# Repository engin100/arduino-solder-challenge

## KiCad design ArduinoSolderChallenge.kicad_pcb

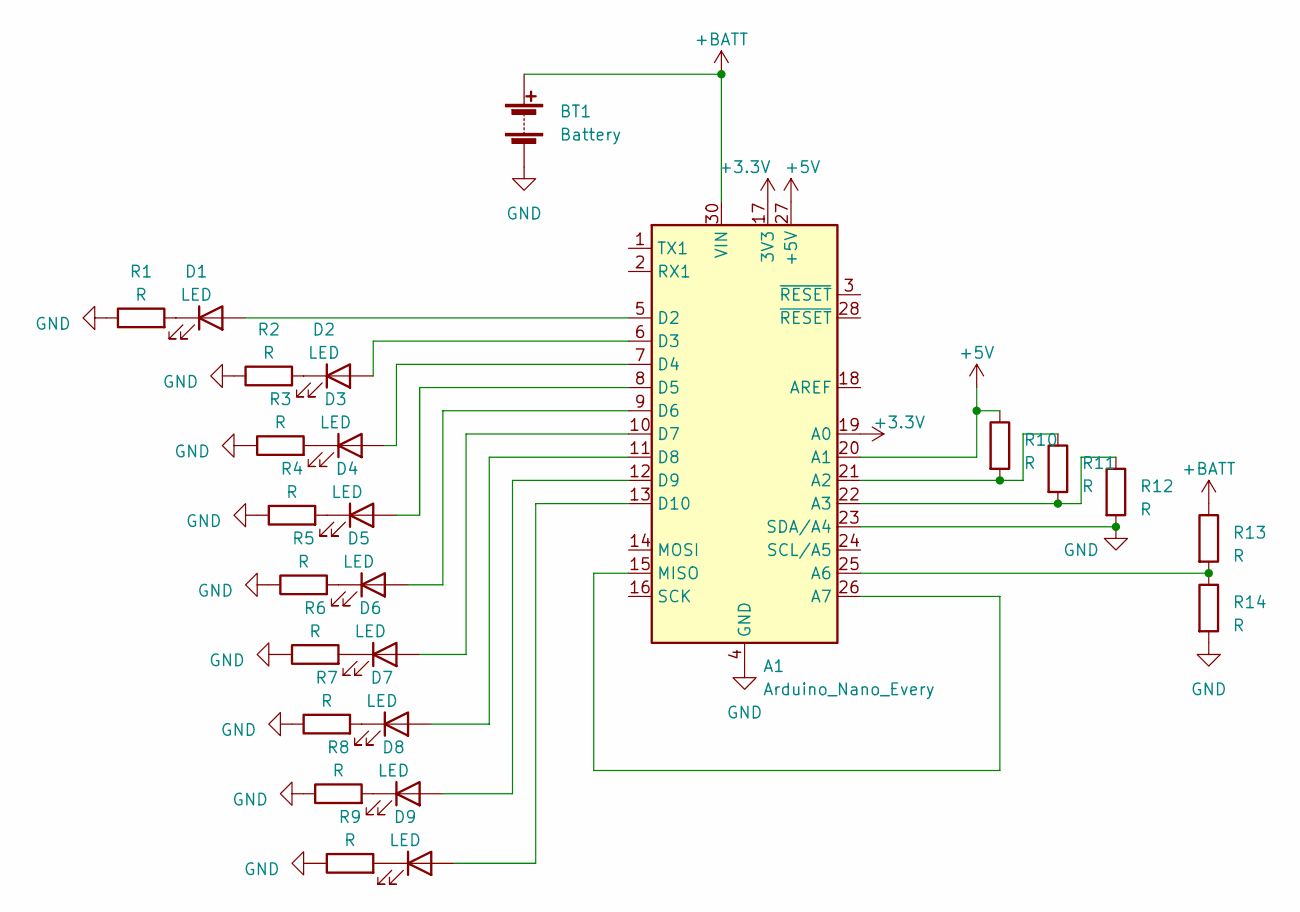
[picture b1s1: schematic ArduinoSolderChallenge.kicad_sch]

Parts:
A1: Arduino_Nano_Every; Arduino_Nano
BT1: Battery; Keystone 967 9V battery holder
D1, D2, D3, D4, D5: LED
D6, D7, D8, D9: LED; LED_1206_3216Metric_Pad1.42x1.75mm_HandSolder
R1, R2, R3, R4, R5, R10, R11, R12: R; Resistor
R6, R7, R8, R9, R13, R14: R; R_1206_3216Metric_Pad1.30x1.75mm_HandSolder

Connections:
+3.3V: A1.17 (3V3), A1.19 (A0)
+5V: A1.20 (A1), A1.27 (+5V), R10.1
+BATT: A1.30 (VIN), BT1.1 (+), R13.1
GND: A1.4 (GND), A1.23 (SDA/A4), A1.29 (GND), BT1.2 (-), R1.1, R2.1, R3.1, R4.1, R5.1, R6.1, R7.1, R8.1, R9.1, R12.2, R14.2
unnamed: A1.21 (A2), R10.2, R11.1
unnamed: A1.22 (A3), R11.2, R12.1
unnamed: A1.25 (A6), R13.2, R14.1
unnamed: A1.15 (MISO), A1.26 (A7)
unnamed: A1.5 (D2), D1.2 (A)
unnamed: A1.6 (D3), D2.2 (A)
unnamed: A1.7 (D4), D3.2 (A)
unnamed: A1.8 (D5), D4.2 (A)
unnamed: A1.9 (D6), D5.2 (A)
unnamed: A1.10 (D7), D6.2 (A)
unnamed: A1.11 (D8), D7.2 (A)
unnamed: A1.12 (D9), D8.2 (A)
unnamed: A1.13 (D10), D9.2 (A)
unnamed: D1.1 (K), R1.2
unnamed: D2.1 (K), R2.2
unnamed: D3.1 (K), R3.2
unnamed: D4.1 (K), R4.2
unnamed: D5.1 (K), R5.2
unnamed: D6.1 (K), R6.2
unnamed: D7.1 (K), R7.2
unnamed: D8.1 (K), R8.2
unnamed: D9.1 (K), R9.2

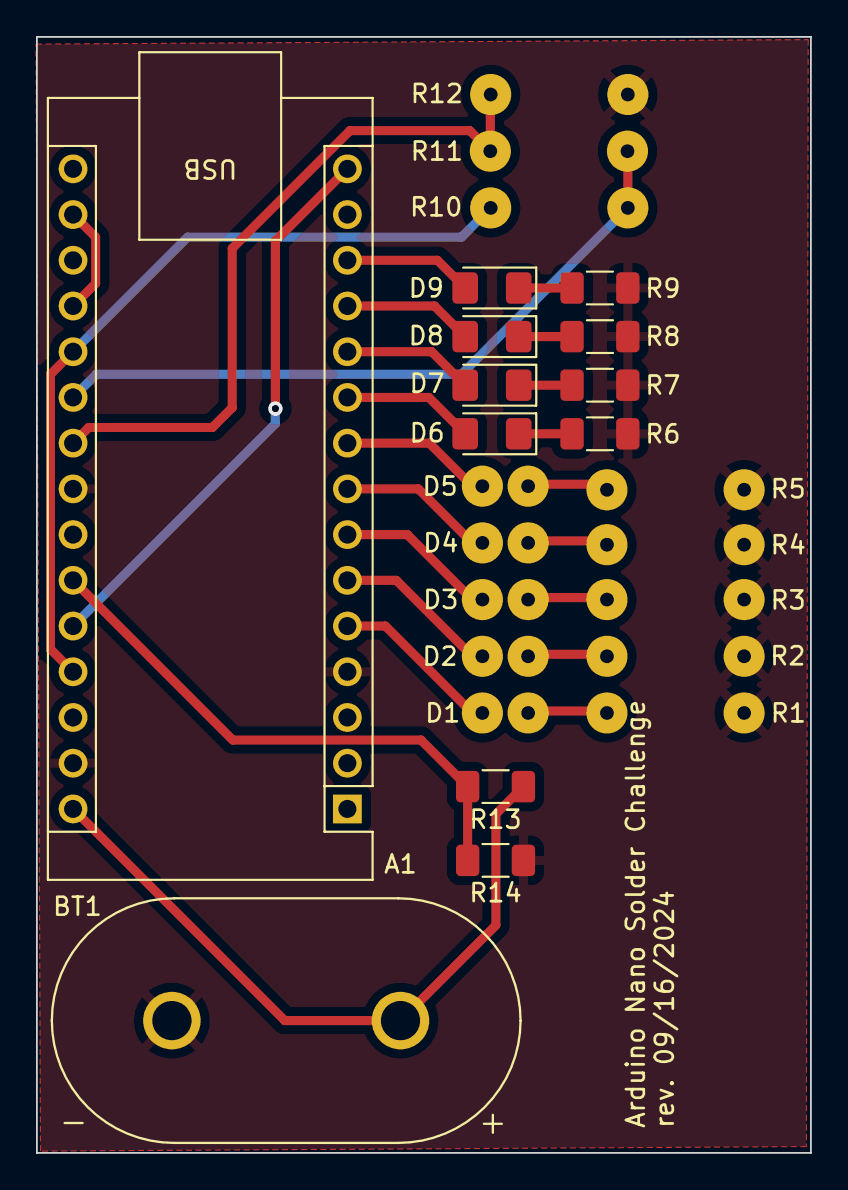
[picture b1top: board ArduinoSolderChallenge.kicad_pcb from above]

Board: 2 copper layers, 43.0 x 62.0 mm, 25 parts (0 on the bottom side), 26 nets.

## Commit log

2024-09-16 intl. commit
